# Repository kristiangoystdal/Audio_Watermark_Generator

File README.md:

# Acoustic Metadata Multiplexer

A low-cost, low-power system for embedding time-synchronized FSK metadata signals into audio recordings made by Autonomous Recording Units (ARUs). Designed for bioacoustic field deployments where cross-unit time synchronization and metadata recovery from audio alone are required.

The system encodes a structured metadata payload as a BFSK signal mixed into the audio recorded by any ARU model — either acoustically via a speaker, or electrically via a 3.5 mm cabled pass-through. A desktop demodulator extracts the metadata from recorded `.wav` files post-deployment.

---

## How It Works

The system operates in a **star topology**: one unit acts as a base station and the others are receivers, one per ARU.

1. **Base station** wakes on a fixed schedule, generates a common payload (message ID, timestamp, user string), and broadcasts it over RF at 433 MHz using the CC1101 transceiver.
2. **Receiver units** listen on the CC1101 in continuous RX mode. On receiving a packet, each receiver generates a BFSK-modulated audio signal encoding the shared payload combined with its own local data (device ID, GPS coordinates, live temperature from DS3231).
3. The FSK signal is mixed into the audio captured by the ARU — either by playing it through a small speaker near the ARU microphone, or by mixing it into a microphone signal over a cabled 3.5 mm connection.
4. Since all receivers embed at the same time (triggered by the same RF packet), the embedded signal appears at the same absolute moment across all ARU recordings — enabling post-hoc time alignment via the message ID.
5. A recorded `.wav` containing the embedded signal can be decoded using the desktop demodulator to recover both the metadata and the synchronization reference point.

**Standalone mode** skips RF communication entirely: the unit generates and embeds its own payload on a fixed schedule, using only locally configured and measured data.

The metadata payload format is:

```
/MID<id>/TIM<timestamp>/STR<string>/DID<device_id>/LOC<lat,lon>/TMP<temperature>/
```

Each field is optional and individually togglable via `user_config.h` or the GUI. `MID` (message ID) is the synchronization anchor — recordings are aligned by matching identical message IDs across units.

---

## Repository Structure

```
Audio_Watermark_Generator/
├── Firmware/                   # STM32G431 embedded firmware
│   ├── Core/
│   │   ├── Inc/                # Headers (drivers, config, DSP)
│   │   └── Src/                # Source (main loop, peripherals, FEC)
│   ├── Drivers/                # HAL, CMSIS, and DSP libraries
│   ├── Middlewares/            # USB device library
│   ├── USB_Device/             # USB CDC interface
│   ├── cmake/                  # CMake toolchain config
│   ├── CMakeLists.txt
│   └── CMakePresets.json
│
├── Hardware/                   # KiCad PCB design
│   ├── *.kicad_sch             # Schematics (MCU, RTC, mixer, speaker, transceiver, battery)
│   ├── *.kicad_pcb             # PCB layout
│   ├── Components/             # Custom footprints, symbols, and 3D models
│   ├── Gerber/                 # Fabrication files
│   └── JCLPCB/                 # BOM and CPL for JLCPCB assembly
│
├── Software/                   # Desktop tools (Python)
│   ├── gui/                    # Configurator and flash tool
│   │   ├── gui.py              # Main GUI application
│   │   ├── build_app.py        # PyInstaller build script
│   │   ├── scripts/            # Config generation, build automation, paths
│   │   └── tools/              # Bundled toolchain (ARM GCC, CMake, Ninja, dfu-util)
│   │
│   └── gui_demodulator/        # Metadata decoder
│       ├── demodulator_gui.py  # Decoder GUI
│       ├── demodulator.py      # FSK demodulation engine
│       └── reed_solomon.py     # Reed-Solomon decoder
│
├── Testing/                    # Test scripts and data
│   ├── scripts/                # Individual test scripts
│   │   └── helper/             # Shared utilities
│   ├── test_files/             # Input audio and measurement data
│   ├── results/                # Output plots and reports
│   └── run_all_tests.py        # Run all tests
│
└── README.md
```

---

## Getting Started

### Prerequisites

| Component       | Requirement                                  |
| --------------- | -------------------------------------------- |
| Microcontroller | STM32G431-based board (custom PCB or Nucleo) |
| Toolchain       | GNU Arm Embedded Toolchain 13.2+             |
| Build system    | CMake + Ninja                                |
| Programmer      | ST-Link V3 or DFU over USB                   |
| Python          | 3.8+ with `tkinter`                          |

### Install Python Dependencies

```bash
pip install numpy scipy matplotlib soundfile
```

> `tkinter` is included with most Python installations. On Linux, you may need `sudo apt install python3-tk`.

---

## Firmware

### Key Configuration

All metadata and system parameters are defined in [`Firmware/Core/Inc/user_config.h`](Firmware/Core/Inc/user_config.h):

| Parameter                                          | Default             | Description                                                           |
| -------------------------------------------------- | ------------------- | --------------------------------------------------------------------- |
| `USER_STRING`                                      | `"Hello World"`     | User-defined string payload                                           |
| `DEVICE_ID`                                        | `42`                | Numeric identifier for this unit                                      |
| `LOCATION`                                         | `"63.4190,10.4015"` | GPS coordinates of this ARU                                           |
| `TEMPERATURE`                                      | `20`                | Static temperature fallback (overridden by DS3231 reading at runtime) |
| `INCLUDE_USER_STRING` / `INCLUDE_DEVICE_ID` / etc. | `true`              | Toggle individual payload fields on/off                               |
| `FSK_LOWER_FREQUENCY`                              | `10000` Hz          | FSK f0 tone (auto-aligned to DAC sample rate)                         |
| `FSK_HIGHER_FREQUENCY`                             | `12000` Hz          | FSK f1 tone (auto-aligned to DAC sample rate)                         |
| `SIGNAL_ATTENUATION`                               | `100`               | Output level (0 = silence, 100 = full)                                |
| `USE_REED_SOLOMON_ERROR_CORRECTION`                | `true`              | Enable/disable RS error correction                                    |
| `RS_ERROR_CORRECTION_SYMBOLS`                      | `20`                | Number of RS parity symbols                                           |
| `OPERATION_MODE`                                   | `0`                 | 0 = Receiver, 1 = Base Station, 2 = Standalone                        |
| `STARTING_HOUR` / `END_HOUR`                       | `0` / `23`          | Daily schedule window (24h format)                                    |
| `RUN_MINUTES` / `SLEEP_MINUTES`                    | `3` / `0`           | Duty cycle within the schedule window                                 |
| `USE_CABLE_TRANSMISSION`                           | `false`             | Cable (3.5 mm) output instead of speaker                              |

You can edit this file manually or use the GUI configurator (see below).

### Operation Modes

**Receiver (`OPERATION_MODE=0`)**
Listens on the CC1101 in continuous RX mode. On receiving a packet, the unit generates a metadata string combining shared fields from the RF packet (message ID, timestamp, user string) with its own local fields (device ID, location, temperature), then outputs the BFSK signal. One receiver unit is deployed at each ARU.

**Base Station (`OPERATION_MODE=1`)**
Wakes on a fixed RTC-based schedule, generates a common payload (message ID, RTC timestamp, user string), and transmits it via the CC1101 RF transceiver. One unit per deployment must be configured as the base station.

**Standalone (`OPERATION_MODE=2`)**
No RF communication. The unit wakes on a fixed RTC-based schedule, generates a payload from locally configured and measured values, and outputs the BFSK signal. Used when cross-unit synchronization is not needed.

### Features

- **BFSK metadata embedding** — DMA-driven circular DAC output with pre-computed sine LUTs; frequencies are auto-aligned to integer samples-per-period for zero spectral leakage
- **Reed-Solomon FEC** — GF(2^8) encoder with configurable parity symbols for burst-error-resilient decoding
- **CC1101 sub-GHz RF** — bit-banged SPI driver for 433 MHz base station to receiver synchronization; receiver uses continuous RX mode
- **DS3231 RTC** — I2C temperature-compensated clock with battery backup; software-controlled power gating to save current between reads
- **Scheduled operation** — configurable active hours (`STARTING_HOUR`/`END_HOUR`) and run/sleep duty cycle aligned to AudioMoth duty-cycle timing; RTC wakeup timer for Base Station/Standalone, GPIO interrupt (GDO0) for Receiver (mode 0)
- **Audio output paths** — speaker (GPIO-switched amplifier) or cable (relay-switched gain-neutral mixing mode with op-amp signal chain)
- **Battery monitoring** — ADC reading through a resistor divider; halts with error code if voltage drops below 3.0 V
- **USB CDC** — serial interface for host communication and first-boot RTC time sync
- **Flash-persistent flags** — records whether time sync has been performed (survives power cycles)
- **LED status codes** — 4-bit binary blink patterns encoding error/status codes, repeated 3 times
- **STOP1 low-power mode** — full peripheral suspend between transmissions; clock and I2C re-initialized on wake

### Build

```bash
cd Firmware
cmake -B build/Debug -S . -G Ninja -DCMAKE_BUILD_TYPE=Debug
cmake --build build/Debug
```

### Flash

**Via ST-Link:**

```bash
openocd -f interface/stlink.cfg -f target/stm32g4x.cfg \
  -c "program build/Debug/Audio_Watermark_Generator.elf verify reset exit"
```

**Via DFU (USB):**
The GUI flash tool handles DFU flashing automatically. Alternatively, use `dfu-util` directly.

---

## Software Tools

### Configurator & Flash Tool

A desktop GUI for configuring metadata parameters and flashing the firmware to the STM32.

```bash
cd Software/gui
python3 gui.py
```

**What it does:**

- Configure metadata fields per operation mode (base station, receiver, standalone)
- Set FSK frequencies, attenuation, and Reed-Solomon error correction
- Set operation schedule (active hours, run/sleep intervals)
- Generate `user_config.h`, build the firmware, and flash over DFU

The tool bundles its own ARM toolchain, CMake, Ninja, and dfu-util in `Software/gui/tools/`, so no manual toolchain setup is needed when using the GUI.

### Metadata Decoder

A desktop GUI for extracting embedded metadata from recorded audio files.

```bash
cd Software/gui_demodulator
python3 demodulator_gui.py
```

**What it does:**

- Load a `.wav` recording containing an embedded BFSK signal
- Perform FSK demodulation and Reed-Solomon decoding
- Display the decoded metadata payload
- Visualize the demodulated spectrum and signal

### Pre-built macOS Apps

Beta `.app` builds are available for macOS:

- **Audio Watermark Flash Tool** — configure and flash
- **FSK Audio Demodulator** — decode metadata from recordings

[Download the latest release](../../releases/latest)

---

## Testing

The `Testing/` directory contains scripts for characterizing and validating system performance.

### Test Scripts

| Script                      | Description                                          |
| --------------------------- | ---------------------------------------------------- |
| `autotest.py`               | Automated demodulator correctness testing            |
| `drift.py`                  | Frequency drift measurement over time                |
| `ecc_burst_test.py`         | Reed-Solomon burst error correction validation       |
| `offset_calculation.py`     | Timing offset between devices                        |
| `localize.py`               | Acoustic localization from multi-receiver recordings |
| `localize_tdoa.py`          | Time-difference-of-arrival (TDOA) localization       |
| `audio_passthrough.py`      | Audio signal chain validation (FFT analysis)         |
| `spec_leak.py`              | Spectral purity and leakage analysis                 |
| `timing.py`                 | Transmission timing validation                       |
| `wakeup.py`                 | Sleep/wakeup mechanism testing                       |
| `plot_fsk_signals.py`       | FSK signal visualization                             |
| `plot_bird_spectrograms.py` | Spectrogram analysis of bird audio                   |
| `plot_current.py`           | Current consumption analysis                         |
| `plot_rssi.py`              | RF signal strength plotting                          |
| `plot_temperature.py`       | Temperature variation analysis                       |

### Test Data

Test input data is organized in `Testing/test_files/`:

- `demodulator_autotest/` — Pre-recorded samples for demodulator validation
- `acoustic_localization/` — Multi-receiver recordings for TDOA testing
- `rtc_measurements/` — RTC drift data
- `range_tests/` — Distance-dependent RF signal quality
- `current_measures/` — Power consumption logs
- `temperature_range/` — Temperature sweep recordings

### Run All Tests

```bash
cd Testing
python3 run_all_tests.py
```

---

## Hardware

The custom 4-layer PCB is designed in KiCad and includes:

- **STM32G431** microcontroller
- **DS3231** RTC with battery backup
- **CC1101** RF transceiver (433 MHz, sub-GHz)
- Audio mixer with gain-neutral pass-through and speaker driver
- USB connector
- Battery power management

Design files are in `Hardware/`:

- Schematics: individual `.kicad_sch` files for each subsystem
- PCB layout: `Audio_watermark_generator.kicad_pcb`
- 3D model: `Audio_watermark_generator.step`
- Fabrication: `Gerber/` directory with Gerber + drill files
- Assembly: `JCLPCB/` with BOM and CPL for JLCPCB ordering
- Custom components: `Components/` with footprints, symbols, and 3D models

---

## Contributing

1. Fork the repository
2. Create a feature branch (`git checkout -b feature/my-feature`)
3. Commit your changes
4. Push and open a pull request

---

## Contributors

- **Kristian Gøystdal** — Developer
- **Einar Bergslid** — Developer

---

## License

Released under the **MIT License**. Free to use, modify, and distribute.

---

`stm32` · `bioacoustics` · `autonomous-recording-unit` · `time-synchronization` · `fsk` · `metadata-embedding` · `reed-solomon` · `kicad` · `python`

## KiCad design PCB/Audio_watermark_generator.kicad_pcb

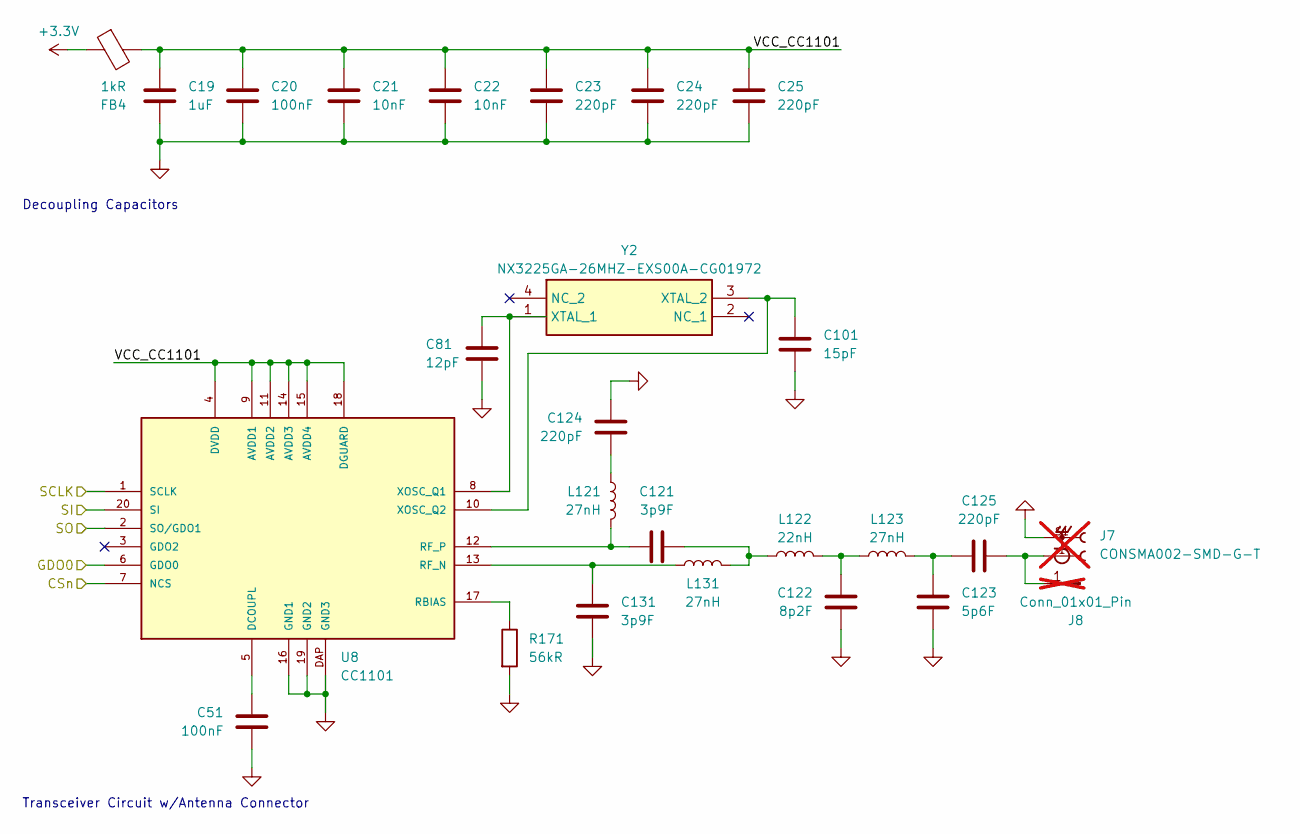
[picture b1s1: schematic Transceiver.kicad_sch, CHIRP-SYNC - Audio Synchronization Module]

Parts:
C19: 1uF; C_0805_2012Metric; LCSC Part # C77079
C20, C51: 100nF; C_0402_1005Metric; LCSC Part # C1525
C21, C22: 10nF; C_0402_1005Metric; LCSC Part # C15195
C23, C24, C25, C124, C125: 220pF; C_0402_1005Metric; LCSC Part # C71693
C81: 12pF; C_0402_1005Metric; LCSC Part # C1547
C101: 15pF; C_0402_1005Metric; LCSC Part # C1548
C121, C131: 3p9F; C_0402_1005Metric; LCSC Part # C85940
C122: 8p2F; C_0402_1005Metric; LCSC Part # C76984
C123: 5p6F; C_0402_1005Metric; LCSC Part # C85941
FB4: 1kR; L_0402_1005Metric; LCSC Part # C76889
J7: CONSMA002-SMD-G-T; LINX_CONSMA002-SMD-G-T; LCSC Part # C6886897; not fitted
J8: Conn_01x01_Pin; TestPoint_Pad_2.0x2.0mm; not fitted
L121, L123, L131: 27nH; L_0402_1005Metric; LCSC Part # C12669
L122: 22nH; L_0402_1005Metric; LCSC Part # C12670
R171: 56kR; R_0402_1005Metric; LCSC Part # C71703
U8: CC1101; LCSC Part # C29953
Y2: NX3225GA-26MHZ-EXS00A-CG01972; Crystal_SMD_3225-4Pin_3.2x2.5mm; Manufacturer_Part_Number NX3225GA-26MHZ-EXS00A-CG01972; LCSC Part # C485372

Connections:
+3.3V: FB4.1; also elsewhere on the board
/STM32/SPI_CSN: U8.7 (NCS); also elsewhere on the board
/STM32/SPI_GOD0: U8.6 (GDO0); also elsewhere on the board
/STM32/SPI_MISO: U8.20 (SI); also elsewhere on the board
/STM32/SPI_MOSI: U8.2 (SO/GDO1); also elsewhere on the board
/STM32/SPI_SCK: U8.1 (SCLK); also elsewhere on the board
/Transceiver/VCC_CC1101: C19.2, C20.2, C21.2, C22.2, C23.2, C24.2, C25.2, FB4.2, U8.4 (DVDD), U8.9 (AVDD1), U8.11 (AVDD2), U8.14 (AVDD3), U8.15 (AVDD4), U8.18 (DGUARD)
GND: C19.1, C20.1, C21.1, C22.1, C23.1, C24.1, C25.1, C51.2, C81.1, C101.2, C122.2, C123.2, C124.1, C131.1, J7.S1, J7.S2, R171.2, U8.16 (GND1), U8.19 (GND2), U8.DAP (GND3); also elsewhere on the board
unnamed: C121.2, L122.1, L131.1
unnamed: C122.1, L122.2, L123.1
unnamed: C123.1, C125.1, L123.2
unnamed: C124.2, L121.2
unnamed: C125.2, J7.1, J8.1
unnamed: C51.1, U8.5 (DCOUPL)
unnamed: R171.1, U8.17 (RBIAS)
unnamed: C131.2, L131.2, U8.13 (RF_N)
unnamed: C121.1, L121.1, U8.12 (RF_P)
unnamed: C81.2, U8.8 (XOSC_Q1), Y2.1 (XTAL_1)
unnamed: C101.1, U8.10 (XOSC_Q2), Y2.3 (XTAL_2)

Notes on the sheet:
Decoupling Capacitors
Transceiver Circuit w/Antenna Connector

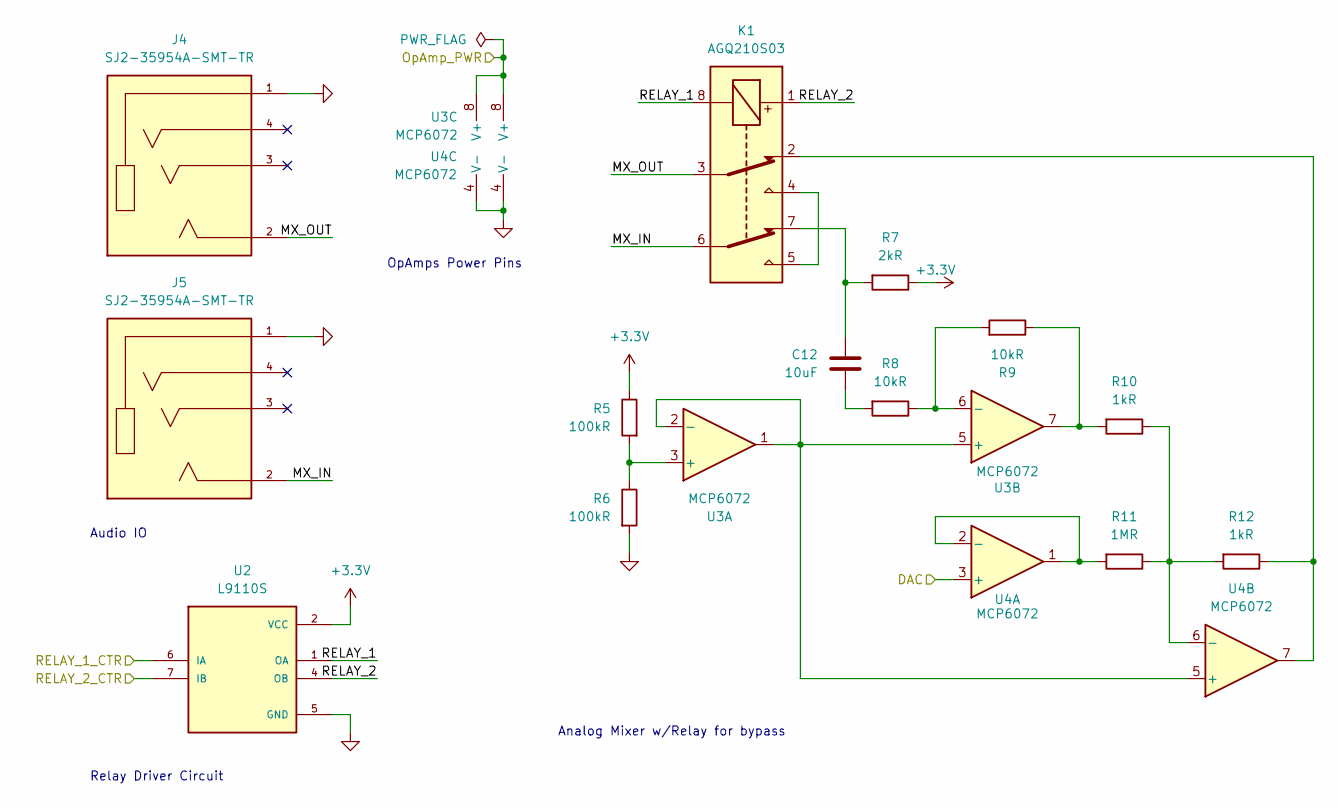
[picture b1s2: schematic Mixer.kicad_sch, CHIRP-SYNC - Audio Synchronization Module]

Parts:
C12: 10uF; C_0805_2012Metric; LCSC Part # C440198
J4, J5: SJ2-35954A-SMT-TR; CUI_SJ2-35954A-SMT-TR; PARTREV 1.04; LCSC Part # C4992345
K1: AGQ210S03; LCSC Part # C5582831
R5, R6: 100kR; R_0805_2012Metric; LCSC Part # C25611
R7: 2kR; R_0805_2012Metric; LCSC Part # C17604
R8, R9: 10kR; R_0805_2012Metric; LCSC Part # C17414
R10, R12: 1kR; R_0805_2012Metric; LCSC Part # C17513
R11: 1MR; R_0805_2012Metric; LCSC Part # C17514
U2: L9110S; SOIC127P599X172-8N; PARTREV NA; LCSC Part # C725793
U3, U4: MCP6072; SOIC127P599X175-8N; LCSC Part # C122875

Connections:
+3.3V: R5.1, R7.1, U2.2 (VCC), U2.3 (VCC); also elsewhere on the board
/Mixer/DAC: U4.3 (+); also elsewhere on the board
/Mixer/MX_IN: J5.2, K1.6
/Mixer/MX_OUT: J4.2, K1.3
/Mixer/OpAmp_PWR: U3.8 (V+), U4.8 (V+); also elsewhere on the board
/Mixer/RELAY_1: K1.8, U2.1 (OA)
/Mixer/RELAY_1_CTR: U2.6 (IA); also elsewhere on the board
/Mixer/RELAY_2: K1.1, U2.4 (OB)
/Mixer/RELAY_2_CTR: U2.7 (IB); also elsewhere on the board
GND: J4.1, J5.1, R6.2, U2.5 (GND), U2.8 (GND), U3.4 (V-), U4.4 (V-); also elsewhere on the board
unnamed: C12.1, K1.7, R7.2
unnamed: C12.2, R8.2
unnamed: K1.2, R12.1, U4.7
unnamed: K1.4, K1.5
unnamed: R9.1, R10.2, U3.7
unnamed: R5.2, R6.1, U3.3 (+)
unnamed: U3.1, U3.2 (-), U3.5 (+), U4.5 (+)
unnamed: R8.1, R9.2, U3.6 (-)
unnamed: R11.2, U4.1, U4.2 (-)
unnamed: R10.1, R11.1, R12.2, U4.6 (-)

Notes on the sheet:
OpAmps Power Pins
Audio IO
Analog Mixer w/Relay for bypass
Relay Driver Circuit

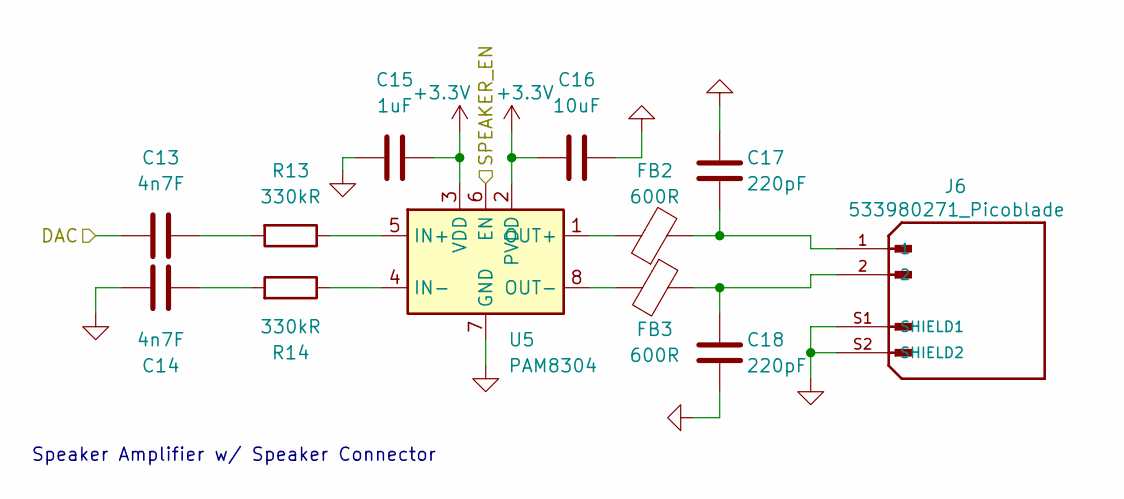
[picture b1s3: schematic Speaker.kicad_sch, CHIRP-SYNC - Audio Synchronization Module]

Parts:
C13, C14: 4n7F; C_0603_1608Metric; LCSC Part # C53987
C15: 1uF; C_0603_1608Metric; LCSC Part # C15849
C16: 10uF; C_0805_2012Metric; LCSC Part # C440198
C17, C18: 220pF; C_0402_1005Metric; LCSC Part # C71693
FB2, FB3: 600R; L_0603_1608Metric; LCSC Part # C1002
J6: 533980271_Picoblade; MOLEX_533980271_Picoblade; PARTREV A; LCSC Part # C122410
R13, R14: 330kR; R_0805_2012Metric; LCSC Part # C17629
U5: PAM8304; PAM8304ASR; LCSC Part # C581342

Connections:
+3.3V: C15.2, C16.1, U5.2 (PVDD), U5.3 (VDD); also elsewhere on the board
/Mixer/DAC: C13.1; also elsewhere on the board
/STM32/SPEAKER_EN: U5.6 (EN); also elsewhere on the board
GND: C14.1, C15.1, C16.2, C17.1, C18.2, J6.S1 (SHIELD1), J6.S2 (SHIELD2), U5.7 (GND); also elsewhere on the board
unnamed: C13.2, R13.2
unnamed: C14.2, R14.2
unnamed: C17.2, FB2.2, J6.1
unnamed: C18.1, FB3.1, J6.2
unnamed: R13.1, U5.5 (IN+)
unnamed: R14.1, U5.4 (IN-)
unnamed: FB2.1, U5.1 (OUT+)
unnamed: FB3.2, U5.8 (OUT-)

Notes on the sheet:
Speaker Amplifier w/ Speaker Connector

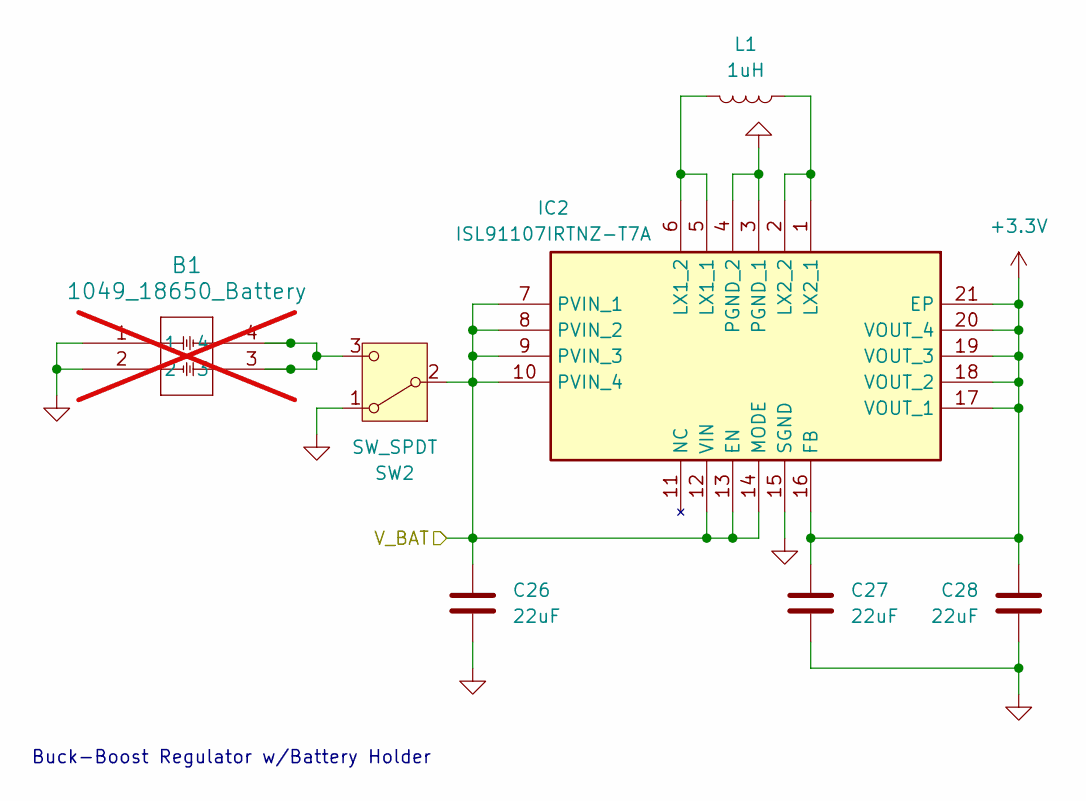
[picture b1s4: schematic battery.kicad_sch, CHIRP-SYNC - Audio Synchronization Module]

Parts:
B1: 1049_18650_Battery; 1049_KEY_1; not fitted
C26, C27, C28: 22uF; C_0603_1608Metric; LCSC Part # C84419
IC2: ISL91107IRTNZ-T7A; QFN50P300X400X80-21N; Manufacturer_Part_Number ISL91107IRTNZ-T7A; Mouser Part Number 968-ISL91107IRTNZT7A
L1: 1uH; L_1008_2520Metric; LCSC Part # C470857
SW2: SW_SPDT; SW_SPDT_PCM12; LCSC Part # C221841

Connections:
+3.3V: C27.1, C28.2, IC2.16 (FB), IC2.17 (VOUT_1), IC2.18 (VOUT_2), IC2.19 (VOUT_3), IC2.20 (VOUT_4), IC2.21 (EP); also elsewhere on the board
/Battery/V_BAT: C26.1, IC2.7 (PVIN_1), IC2.8 (PVIN_2), IC2.9 (PVIN_3), IC2.10 (PVIN_4), IC2.12 (VIN), IC2.13 (EN), IC2.14 (MODE), SW2.2 (B); also elsewhere on the board
GND: B1.1, B1.2, C26.2, C27.2, C28.1, IC2.3 (PGND_1), IC2.4 (PGND_2), IC2.15 (SGND), SW2.1 (A); also elsewhere on the board
unnamed: IC2.5 (LX1_1), IC2.6 (LX1_2), L1.2
unnamed: IC2.1 (LX2_1), IC2.2 (LX2_2), L1.1
unnamed: B1.3, B1.4, SW2.3 (C)

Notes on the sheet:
Buck-Boost Regulator w/Battery Holder

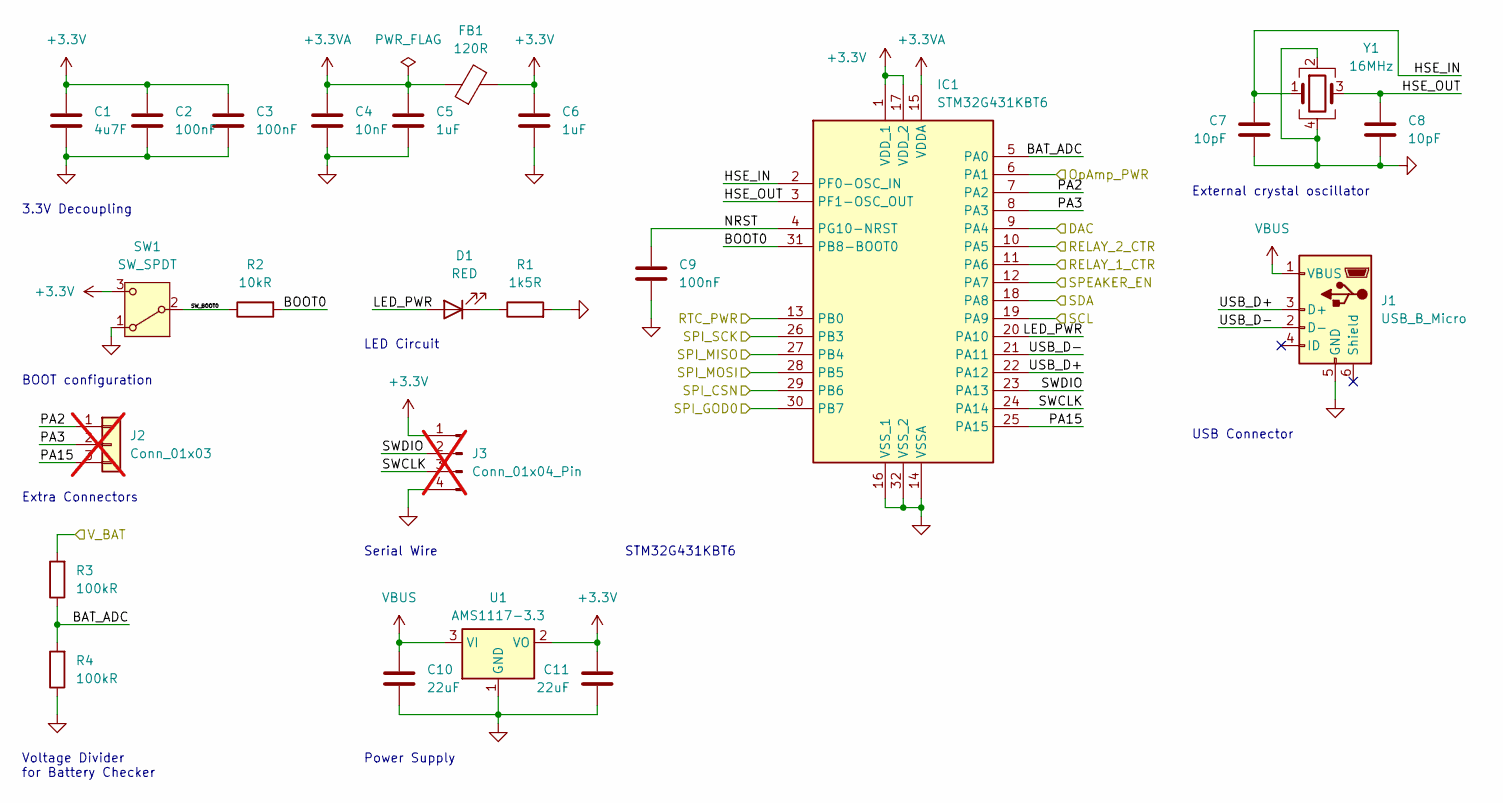
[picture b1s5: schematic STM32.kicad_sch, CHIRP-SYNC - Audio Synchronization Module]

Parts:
C1: 4u7F; C_0603_1608Metric; LCSC Part # C19666
C2, C3, C9: 100nF; C_0402_1005Metric; LCSC Part # C1525
C4: 10nF; C_0402_1005Metric; LCSC Part # C15195
C5, C6: 1uF; C_0603_1608Metric; LCSC Part # C15849
C7, C8: 10pF; C_0402_1005Metric; LCSC Part # C32949
C10, C11: 22uF; C_0805_2012Metric; LCSC Part # C45783
D1: RED; LED_0603_1608Metric; LCSC Part # C2286
FB1: 120R; L_0603_1608Metric; LCSC Part # C14709
IC1: STM32G431KBT6; Manufacturer_Part_Number STM32G431KBT6; Mouser Part Number 511-STM32G431KBT6
J1: USB_B_Micro; USB_Micro-B_Wuerth_629105150521; LCSC Part # C2894326
J2: Conn_01x03; PinHeader_1x03_P2.54mm_Vertical_SMD_Pin1Right; not fitted
J3: Conn_01x04_Pin; PinHeader_1x04_P2.54mm_Vertical; not fitted
R1: 1k5R; R_0402_1005Metric; LCSC Part # C25867
R2: 10kR; R_0402_1005Metric; LCSC Part # C25744
R3, R4: 100kR; R_0805_2012Metric; LCSC Part # C25611
SW1: SW_SPDT; SW_SPDT_PCM12; LCSC Part # C221841
U1: AMS1117-3.3; SOT-223-3_TabPin2; LCSC Part # C6186
Y1: 16MHz; Crystal_SMD_3225-4Pin_3.2x2.5mm; LCSC Part # C112972

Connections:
+3.3V: C1.1, C2.1, C3.1, C6.1, C11.1, FB1.2, IC1.1 (VDD_1), IC1.17 (VDD_2), J3.1, SW1.3 (C), U1.2 (VO); also elsewhere on the board
+3.3VA: C4.1, C5.1, FB1.1, IC1.15 (VDDA)
/Battery/V_BAT: R3.2; also elsewhere on the board
/Mixer/DAC: IC1.9 (PA4); also elsewhere on the board
/Mixer/OpAmp_PWR: IC1.6 (PA1); also elsewhere on the board
/Mixer/RELAY_1_CTR: IC1.11 (PA6); also elsewhere on the board
/Mixer/RELAY_2_CTR: IC1.10 (PA5); also elsewhere on the board
/RTC/RTC_PWR: IC1.13 (PB0); also elsewhere on the board
/RTC/SCL: IC1.19 (PA9); also elsewhere on the board
/RTC/SDA: IC1.18 (PA8); also elsewhere on the board
/STM32/BAT_ADC: IC1.5 (PA0), R3.1, R4.2
/STM32/BOOT0: IC1.31 (PB8-BOOT0), R2.2
/STM32/HSE_IN: C7.2, IC1.2 (PF0-OSC_IN), Y1.1
/STM32/HSE_OUT: C8.1, IC1.3 (PF1-OSC_OUT), Y1.3
/STM32/LED_PWR: D1.2 (A), IC1.20 (PA10)
/STM32/NRST: C9.1, IC1.4 (PG10-NRST)
/STM32/PA2: IC1.7 (PA2), J2.1
/STM32/PA3: IC1.8 (PA3), J2.2
/STM32/PA15: IC1.25 (PA15), J2.3
/STM32/SPEAKER_EN: IC1.12 (PA7); also elsewhere on the board
/STM32/SPI_CSN: IC1.29 (PB6); also elsewhere on the board
/STM32/SPI_GOD0: IC1.30 (PB7); also elsewhere on the board
/STM32/SPI_MISO: IC1.27 (PB4); also elsewhere on the board
/STM32/SPI_MOSI: IC1.28 (PB5); also elsewhere on the board
/STM32/SPI_SCK: IC1.26 (PB3); also elsewhere on the board
/STM32/SWCLK: IC1.24 (PA14), J3.3
/STM32/SWDIO: IC1.23 (PA13), J3.2
/STM32/SW_BOOT0: R2.1, SW1.2 (B)
/STM32/USB_D+: IC1.22 (PA12), J1.3 (D+)
/STM32/USB_D-: IC1.21 (PA11), J1.2 (D-)
GND: C1.2, C2.2, C3.2, C4.2, C5.2, C6.2, C7.1, C8.2, C9.2, C10.2, C11.2, IC1.14 (VSSA), IC1.16 (VSS_1), IC1.32 (VSS_2), J1.5 (GND), J3.4, R1.2, R4.1, SW1.1 (A), U1.1 (GND), Y1.2, Y1.4; also elsewhere on the board
unnamed: D1.1 (K), R1.1
VBUS: C10.1, J1.1 (VBUS), U1.3 (VI)

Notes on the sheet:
Power Supply
STM32G431KBT6
USB Connector
LED Circuit
BOOT configuration
Voltage Divider for Battery Checker
External crystal oscillator
Extra Connectors
Serial Wire
3.3V Decoupling

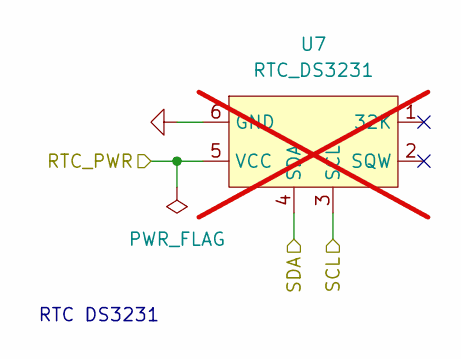
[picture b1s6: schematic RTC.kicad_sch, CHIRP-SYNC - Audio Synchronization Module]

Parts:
U7: RTC_DS3231; PinHeader_1x06_P2.54mm_DS3231; not fitted

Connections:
/RTC/RTC_PWR: U7.5 (VCC); also elsewhere on the board
/RTC/SCL: U7.3 (SCL); also elsewhere on the board
/RTC/SDA: U7.4 (SDA); also elsewhere on the board
GND: U7.6 (GND); also elsewhere on the board

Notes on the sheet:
RTC DS3231

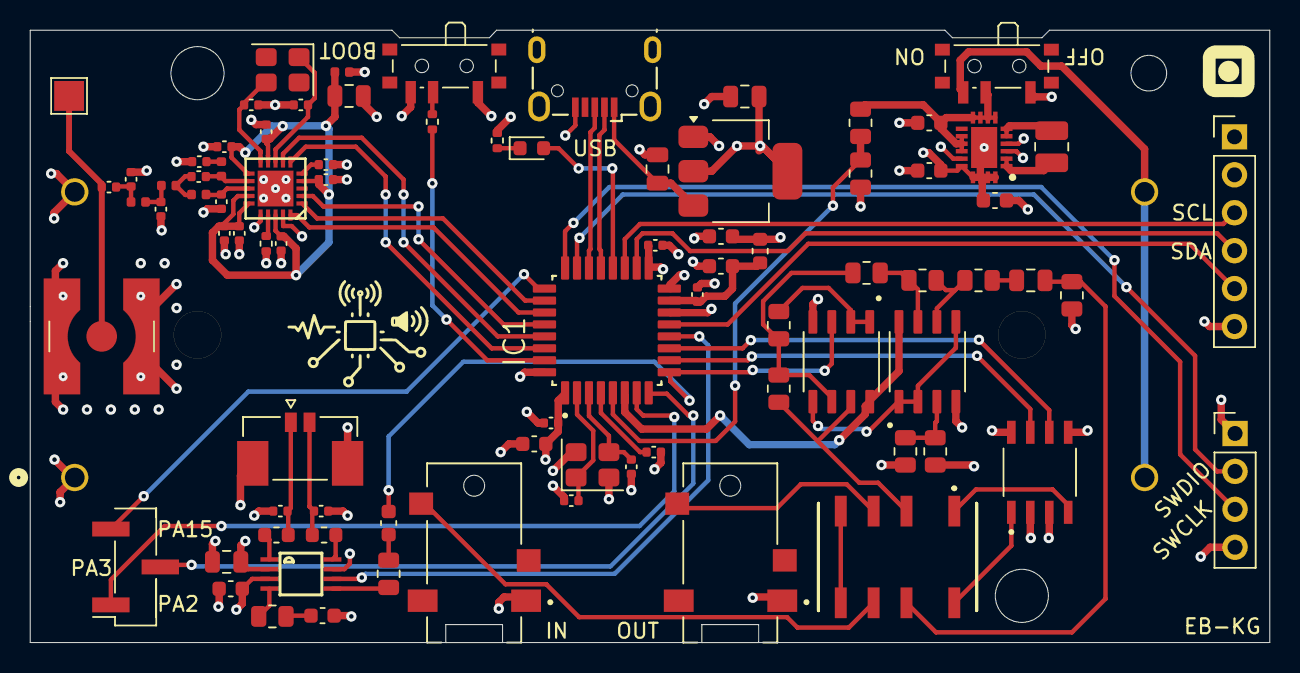
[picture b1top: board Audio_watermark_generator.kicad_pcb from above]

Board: 4 copper layers, 83.0 x 41.0 mm, 85 parts (1 on the bottom side), 70 nets.

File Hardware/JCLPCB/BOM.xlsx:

Reference | Qty | Value | DNP | Footprint | LCSC Part #
 |  |  | DNP
C1 | 1 | 4u7F |  | Capacitor_SMD:C_0603_1608Metric | C19666
C2,C3,C9,C20,C51 | 5 | 100nF |  | Capacitor_SMD:C_0402_1005Metric | C1525
C4,C21,C22 | 3 | 10nF |  | Capacitor_SMD:C_0402_1005Metric | C15195
C5,C6,C15 | 3 | 1uF |  | Capacitor_SMD:C_0603_1608Metric | C15849
C7,C8 | 2 | 10pF |  | Capacitor_SMD:C_0402_1005Metric | C32949
C10,C11 | 2 | 22uF |  | Capacitor_SMD:C_0805_2012Metric | C45783
C12,C16 | 2 | 10uF |  | Capacitor_SMD:C_0805_2012Metric | C440198
C13,C14 | 2 | 4n7F |  | Capacitor_SMD:C_0603_1608Metric | C53987
C17,C18,C23,C24,C25,C124,C125 | 7 | 220pF |  | Capacitor_SMD:C_0402_1005Metric | C71693
C19 | 1 | 1uF |  | Capacitor_SMD:C_0805_2012Metric | C77079
C26,C27,C28 | 3 | 22uF |  | Capacitor_SMD:C_0603_1608Metric | C84419
C81 | 1 | 12pF |  | Capacitor_SMD:C_0402_1005Metric | C1547
C101 | 1 | 15pF |  | Capacitor_SMD:C_0402_1005Metric | C1548
C121,C131 | 2 | 3p9F |  | Capacitor_SMD:C_0402_1005Metric | C85940
C122 | 1 | 8p2F |  | Capacitor_SMD:C_0402_1005Metric | C76984
C123 | 1 | 5p6F |  | Capacitor_SMD:C_0402_1005Metric | C85941
D1 | 1 | RED |  | LED_SMD:LED_0603_1608Metric | C2286
FB1 | 1 | 120R |  | Inductor_SMD:L_0603_1608Metric | C14709
FB2,FB3 | 2 | 600R |  | Inductor_SMD:L_0603_1608Metric | C1002
FB4 | 1 | 1kR |  | Inductor_SMD:L_0402_1005Metric | C76889
IC1 | 1 | STM32G431KBT6 |  | QFP80P900X900X160-32N | C529357
IC2 | 1 | ISL91107IRTNZ-T7A |  | QFN50P300X400X80-21N | C2071659
J1 | 1 | USB_B_Micro |  | USB_Micro-B_Wuerth_629105150521 | C2894326
 |  |  | DNP
 |  |  | DNP
J4,J5 | 2 | SJ2-35954A-SMT-TR |  | CUI_SJ2-35954A-SMT-TR | C4992345
J6 | 1 | 533980271_Picoblade |  | MOLEX_533980271_Picoblade | C122410
 |  |  | DNP
 |  |  | DNP
K1 | 1 | AGQ210S03 |  | AGQ210S03 | C5582831
L1 | 1 | 1uH |  | Inductor_SMD:L_1008_2520Metric | C470857
L121,L123,L131 | 3 | 27nH |  | Inductor_SMD:L_0402_1005Metric | C12669
L122 | 1 | 22nH |  | Inductor_SMD:L_0402_1005Metric | C12670
R1 | 1 | 1k5R |  | Resistor_SMD:R_0402_1005Metric | C25867
R2 | 1 | 10kR |  | Resistor_SMD:R_0402_1005Metric | C25744
R3,R4,R5,R6 | 4 | 100kR |  | Resistor_SMD:R_0805_2012Metric | C25611
R7 | 1 | 2kR |  | Resistor_SMD:R_0805_2012Metric | C17604
R8,R9 | 2 | 10kR |  | Resistor_SMD:R_0805_2012Metric | C17414
R10,R12 | 2 | 1kR |  | Resistor_SMD:R_0805_2012Metric | C17513
R11 | 1 | 1MR |  | Resistor_SMD:R_0805_2012Metric | C17514
R13,R14 | 2 | 330kR |  | Resistor_SMD:R_0805_2012Metric | C17629
R171 | 1 | 56kR |  | Resistor_SMD:R_0402_1005Metric | C71703
SW2,SW1 | 2 | SW_SPDT |  | SW_SPDT_PCM12 | C221841
U1 | 1 | AMS1117-3.3 |  | Package_TO_SOT_SMD:SOT-223-3_TabPin2 | C6186
U2 | 1 | L9110S |  | Driver:SOIC127P599X172-8N | C725793
U3,U4 | 2 | MCP6072 |  | OpAmp:SOIC127P599X175-8N | C122875
U5 | 1 | PAM8304 |  | Audio_Module:PAM8304ASR | C581342
 |  |  | DNP
U8 | 1 | CC1101 |  | RF_Module:CC1101 | C29953
Y1 | 1 | 16MHz |  | Crystal:Crystal_SMD_3225-4Pin_3.2x2.5mm | C112972
Y2 | 1 | 26Mhz |  | Crystal:Crystal_SMD_3225-4Pin_3.2x2.5mm | C485372

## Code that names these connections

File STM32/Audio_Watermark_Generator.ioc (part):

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Mcu.Name=STM32G431K(6-8-B)Tx
Mcu.Package=LQFP32
Mcu.UserName=STM32G431KBTx
PA0.Mode=IN1-Single-Ended
PA0.Signal=ADC1_IN1
PA1.Signal=GPIO_Output
PA10.Signal=GPIO_Output
PA11.Mode=Device
PA11.Signal=USB_DM
PA12.Mode=Device
PA12.Signal=USB_DP
PA13.Mode=Serial_Wire
PA13.Signal=SYS_JTMS-SWDIO
PA14.Mode=Serial_Wire
PA14.Signal=SYS_JTCK-SWCLK
PA15.Signal=GPIO_Output
PA2.Mode=Asynchronous
PA2.Signal=USART2_TX
PA3.Mode=Asynchronous
PA3.Signal=USART2_RX
PA4.Signal=COMP_DAC11_group
PA5.Signal=GPIO_Output
PA6.Signal=GPIO_Output
PA7.Signal=GPIO_Output
PA8.Mode=I2C
PA8.Signal=I2C2_SDA
PA9.Mode=I2C
PA9.Signal=I2C2_SCL
PB0.Signal=GPIO_Output
PB3.Signal=GPIO_Output
PB4.Signal=GPIO_Output
PB5.Signal=GPIO_Input
PB6.Signal=GPIO_Output
PB7.Signal=GPXTI7
PF0-OSC_IN.Mode=HSE-External-Oscillator
PF0-OSC_IN.Signal=RCC_OSC_IN
PF1-OSC_OUT.Mode=HSE-External-Oscillator
PF1-OSC_OUT.Signal=RCC_OSC_OUT
RCC.HSE_VALUE=16000000
RCC.SYSCLKFreq_VALUE=96000000
RCC.SYSCLKSource=RCC_SYSCLKSOURCE_PLLCLK
board=custom

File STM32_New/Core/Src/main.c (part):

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  __HAL_RCC_GPIOA_CLK_ENABLE();
  __HAL_RCC_GPIOB_CLK_ENABLE();

  /*Configure GPIO pins : PF0 PF1 */
  GPIO_InitStruct.Pin = GPIO_PIN_0 | GPIO_PIN_1;
  GPIO_InitStruct.Mode = GPIO_MODE_ANALOG;
  GPIO_InitStruct.Pull = GPIO_NOPULL;
  HAL_GPIO_Init(GPIOF, &GPIO_InitStruct);

  /*Configure GPIO pin : PG10 */
  GPIO_InitStruct.Pin = GPIO_PIN_10;
  GPIO_InitStruct.Mode = GPIO_MODE_ANALOG;
  GPIO_InitStruct.Pull = GPIO_NOPULL;
  HAL_GPIO_Init(GPIOG, &GPIO_InitStruct);

  /*Configure GPIO pins : PA0 PA5 PA6 PA7
                           PA8 PA9 PA10 PA11
                           PA12 PA13 PA14 PA15 */
  GPIO_InitStruct.Pin = GPIO_PIN_0 | GPIO_PIN_5 | GPIO_PIN_6 | GPIO_PIN_7 |
                        GPIO_PIN_8 | GPIO_PIN_9 | GPIO_PIN_10 | GPIO_PIN_11 |
                        GPIO_PIN_12 | GPIO_PIN_13 | GPIO_PIN_14 | GPIO_PIN_15;
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  GPIO_InitStruct.Pull = GPIO_NOPULL;
  HAL_GPIO_Init(GPIOA, &GPIO_InitStruct);

  /*Configure GPIO pin : PA1 */
  GPIO_InitStruct.Pin = GPIO_PIN_1;
  GPIO_InitStruct.Mode = GPIO_MODE_IT_FALLING;
  GPIO_InitStruct.Pull = GPIO_PULLUP;
  HAL_GPIO_Init(GPIOA, &GPIO_InitStruct);

  /*Configure GPIO pins : PB0 PB3 PB4 PB5
                           PB6 PB7 PB8 */
  GPIO_InitStruct.Pin = GPIO_PIN_0 | GPIO_PIN_3 | GPIO_PIN_4 | GPIO_PIN_5 |
                        GPIO_PIN_6 | GPIO_PIN_7 | GPIO_PIN_8;
  GPIO_InitStruct.Mode = GPIO_MODE_ANALOG;
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
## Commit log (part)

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2026-03-06 implement battery voltage reading and low battery detection
2026-03-06 fix: cast ADC value to unsigned long for printf compatibility
2026-03-09 update function list and add PLL source configuration for improved signal processing
2026-03-09 refactor: enhance GUI layout and add attenuation settings
2026-03-11 Implement Reed-Solomon codec functions for encoding and decoding
2026-03-11 Add debug prints for frequency band search and plot scores in FSK decoding
2026-03-11 add Reed-Solomon error correction configuration for improved data reliability
2026-03-12 update Reed-Solomon error correction symbols to improve data efficiency
2026-03-12 refactor frequency pair calculation to enhance clarity and add handling for equal period counts
2026-03-12 refactor frequency adjustment functions for improved clarity and accuracy
2026-03-13 enhance frequency pair calculation with tolerance checks for sample accuracy
2026-03-17 Refactor relay control functions to improve clarity and maintainability
2026-03-17 Change PA1 signal from GPIO_Input to GPIO_Output for proper configuration
2026-03-18 Implement best offset search for FSK decoding and adjust symbol alignment
2026-03-18 Update NSYM value to 20 for improved Reed-Solomon codec performance
2026-03-18 Add RTC driver source files to STM32_Drivers source list
2026-03-18 Refactor FSK timing and offset selection: replace select_best_f0_setup with select_best_symbol_timing_and_offset for improved accuracy; adjust avg_bin_width in refine_fsk_tones_fft
2026-03-19 Add venv directory to .gitignore to prevent virtual environment files from being tracked
2026-03-20 Remove test suite for GUI synchronization of audio files
2026-03-20 Refactor user config handling: Update GUI variable access and add attenuation and error correction settings
2026-03-23 Add determinate progress bar and message count to demodulator GUI
    Add progress_callback parameter to decode_fsk, find_likely_fsk_region,
    and select_best_symbol_timing_and_offset to report progress as a
    fraction. The GUI now shows a determinate progress bar with phase
    descriptions instead of an indeterminate spinner. decode_fsk returns
    the number of successfully decoded messages, displayed in the status
    text after each run.
2026-03-25 Update PCB settings and add new VIP net class
2026-04-10 Refactor build and flash process by removing OpenOCD dependencies and integrating dfu-util for USB flashing
2026-04-13 Adjust output segment size and optimize memory allocation for sine wave lookup tables
2026-04-14 Enhance flash_only function to support conditional leave parameter and improve run_with_log error handling
2026-04-14 Refactor SPI functions to remove unused parameters and simplify implementation; streamline error handling and CS pin management
2026-04-14 Implement error handling in battery, radio, and main modules; add EXTI interrupt handler for GPIO
2026-04-15 Refactor radio module: rename functions for clarity and implement payload building logic
2026-04-15 Refactor DS3231 module: rename functions for consistency and clarity, and remove unused functions
2026-04-15 Refactor main.c: reorganize includes, enhance logging for RTC initialization, and streamline stop mode handling
2026-04-15 Refactor radio and module handling for clarity and consistency (#126)
    * Refactor RX mode handling in main function and streamline TX process in radio module
    * Add validation for watermark fields in FlashToolApp
    * Refactor radio module: rename functions for clarity and implement payload building logic
    * Add CC1101 configuration structure and register settings for RX and TX modes
    * Refactor function names in battery, frequency_config, opamps, reed_solomon, and relay modules for consistency and clarity
    * Refactor CC1101 module: replace SPI functions with bit-bang implementation and improve pin state macros
2026-04-15 Enhance TX mode configuration and improve STOP mode handling in main loop (#130)
2026-04-16 Add USB Device Library support for STM32G4 series
2026-04-16 feat: Add delay in power on/off functions for DS3231 initialization
2026-04-20 Add temperature reading from DS3231 in main loop
2026-04-20 Improve DS3231 power-on sequence and enhance error logging for time read failures
2026-04-21 Refactor Radio_Receive function to improve GDO0 wait logic and increase timeout for stability
2026-04-22 Update CC1101 sync word configuration for improved uniqueness
2026-04-22 Refactor Radio_Receive function to simplify GDO0 handling and remove redundant logging
2026-04-22 Reduce SYNC_DELAY_MS and refactor audio transmission functions for improved timing and clarity
2026-04-22 Autotest (#138)
    * Refactor FSK region detection and decoding process for improved clarity and performance
    * Add autotest script to decode FSK from WAV files in AUTOTEST folder
2026-04-23 Remove unnecessary delay in Opamps_Disable function for improved responsiveness
2026-04-24 Fix threshold calculation and enhance message printing to include Message ID
2026-04-29 Set interval to 1 when using default interval in user configuration
2026-04-29 Implement wakeup timer functionality with initialization, minute calculation, and validation checks
2026-04-30 Comment out logging statements in Opamps and Relay functions
2026-04-30 Update IOCFG0 configuration for improved packet reception handling
2026-05-01 142 fix wakeup timer for tx (#145)
    * Rename interval and frequency widgets for clarity and consistency in the FlashToolApp
    * Fix wakeup timer logic and add delayed start handling for TX and Standalone modes
    * Set interval to 1 when using default interval in user configuration
    * Add wakeup.c to user source files in CMake configuration
    * Refactor frequency configuration comments for clarity in CC1101 settings
    * Add logging for time read from DS3231 in DS3231_GetTime function
2026-05-04 enhance time synchronization process with improved port detection and readback validation
2026-05-04 remove unused complete_tick calculation in main function
2026-05-06 Add coherent FSK demodulator as a drop-in replacement for demodulator.py
2026-05-07 Update schedule settings label to include UTC and adjust datetime handling for time synchronization
2026-05-11 Update wire and label positions in Mixer schematic for improved layout
2026-05-12 Add LED indication for error state in Error_Handler
2026-05-12 Add wait_miso_low calls to ensure MISO is low before operations in CC1101 functions
2026-05-13 Adjust DS3231 initialization and synchronization timing; enable I2C2 clock
2026-05-14 Improve demodulator robustness and add silent-mode support
    - Add DEBUG_PRINTS constant (default True) with _dprint/_dwrite helpers so
    all diagnostic output can be silenced programmatically (used by autotest)
    - Add DAC_FS module-level constant; update compute_p0 to use it
    - find_message_ranges: add minimum reliable-symbol filter (MIN_MESSAGE_BITS×2),
    max-length filter (256 bytes), and _trim_sparse_flanks to strip small noise
    clusters separated by gaps ≥20 bits from the leading/trailing edges of a range
2026-05-16 Remove unused transmission variables and initial time settings from user configuration
2026-05-16 Enhance payload string creation to include RSSI value and add XTAL frequency calibration
2026-05-19 Add noisy audio generator, autotest results, and result plotter
    - create_speaker_noisy.py: generates SPEAKER_NOISY by adding white noise
    at a target SNR using bandpass-estimated FSK signal power
    - plot_autotest.py: plots message decode rate vs. SNR from autotest CSV output
    - autotest_SPEAKER_20260514_174215.csv: baseline autotest results across
    4 frequency pairs and SNR range +2 to -8 dB
2026-05-25 Refactor autotest scripts to improve noise handling and enhance CSV plotting functionality
2026-05-26 Add module green and yellow CSV files for range tests
2026-05-26 Refactor import statements to use absolute paths for helper module across multiple scripts
2026-05-26 Add new audio test files for various configurations and scenarios
2026-05-26 Refactor code structure for improved readability and maintainability
2026-05-26 Add run_all_tests.py script to execute all test scripts in the 'scripts' folder
2026-05-26 Rename folder from Python to Software
2026-05-26 Remove old acoustic localization and GUI demodulator scripts
2026-05-26 Add demodulator autotest files to .gitignore
2026-05-27 Fix Pylance type errors and average repeated autotest runs in plots (#158)
    - Wrap lfilter() result in np.asarray() so Pylance resolves .std() correctly
    - Change main() return type from None to int to match return 0 statements
    - Add assert m is not None after FOLDER_RE.match() (subfolders are pre-filtered)
    - Group autotest CSV files by prefix (autotest_<type>_) before plotting so
    multiple runs are averaged into a single curve instead of plotted separately
    - Add pyrightconfig.json to .gitignore
2026-05-27 Automate toolchain setup and fix path issues in configuration (#159)
    * Enhance setup_toolchain.sh to automate tool downloads and installations for ARM GNU Toolchain, CMake, Ninja, and dfu-util
    * Update STM32Tool.spec to correct data path from ../../STM32 to ../../Firmware
    * Update paths.py to correct PROJECT_SRC directory from STM32 to Firmware
2026-05-30 Refactor localization script to process bird detections from subfolders, update calibration handling, and improve documentation
2026-05-30 Refactor main loop logging and add RTC timing check for testing
2026-06-02 Fix datetime parsing in offset calculation and update plot title
2026-06-02 Update drift.py and auto_drift.py: Adjust log duration and module color; enhance logging output formatting
2026-06-02 Add synchronized audio segments for clap tests in echo room
2026-06-02 Enhance TDOA localization scripts and improve RTC drift analysis (#162)
    * Add direction TDOA localization script with audio processing and plotting
    * Update RTC Drift Analyzer and auto-drift script for improved functionality and organization
    * Refactor TDOA localization to use nonlinear least-squares optimization and update docstring
    * Fix datetime parsing in offset calculation and update plot title
    * Remove titles from plots and update distance units from cm to m in plot functions
    * Remove coherent demodulator implementation and related functionality
2026-06-03 Enhance ECC burst error correction tests and improve accuracy (#164)
    * Add ECC burst error correction test and related WAV files
    * Improve ECC burst test accuracy with payload validation
    Add reference-payload comparison in _decode_audio so that a corrupted
    decode which still contains valid field markers (false positive) is
    rejected unless it matches the clean reference exactly. Refactor
    _count_valid_messages into _get_message_payloads to return actual
2026-06-07 Add RTC drift measurement logs for June 2, 2026
2026-06-07 Enhance FSK demodulation, error handling, and add temperature plotting (#166)
    * Adjust FSK demodulation parameters and improve error handling in time parsing
    * Refactor code structure for improved readability and maintainability
    * Add temperature plotting script with data parsing and visualization
    * Add RTC drift measurement logs for June 2, 2026
    * Update drift directory path for RTC drift analysis
    * Update .gitignore to specify firmware text files and clean up formatting
2026-06-07 Refactor header files by removing redundant comments for improved clarity

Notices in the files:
STM32_New/Core/Src/main.c:
Copyright (c) 2026 STMicroelectronics.
All rights reserved.
This software is licensed under terms that can be found in the LICENSE file
